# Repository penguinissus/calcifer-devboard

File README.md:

# Calcifer Devboard
Calcifer Devboard is a funny take on the RP2040 Devboard. It contains all of the basic components of what a devboard usually has like SRAM, processors, USB controllers, and breakout pins. The interesting twist on this devboard is that it is shaped like Calcifer, a character from Howl's Moving Castle.  

# Features
- USB-C Port  
- 12MHz Crystal Oscillator  
- 16mb Flash Storage
- 29 I/O Pins  

# Why did I make it
If you don't know the story behind Howl's Moving Castle, Calcifer is a fire demon that is trapped inside Howl's Castle and he powers and controls all of the magical things that the castle does. To me, this seemed parallel to what a devboard does in any electronics project, since a devboard is basically the heart and soul and would control all of the other components around it. 

# Diagrams
This schematic diagram looks the exact same as the guide from kaipereira.  
  
This is what my devboard looked like in the PCB editor. You can see that it has the outline and silkscreen of calcifer on it.  
  
This is what the front of the PCB should look like when it is built properly. The frontside only shows a silkscreen of calcifer and is not obstructed by any components.  
  
This is what the back of the PCB should look like. All of the components are on this side and all of the pins are clearly labeled. There is also a label saying this is made by me.  

# Resource
This project is all thanks to [kaipereira's guide](https://github.com/KaiPereira/build-a-devboard/blob/master/README.md) on designing an RP2040 devboard. 

# How to use
This is just a devboard so there isn't really a step-by-step assembly or firmware isntructions.

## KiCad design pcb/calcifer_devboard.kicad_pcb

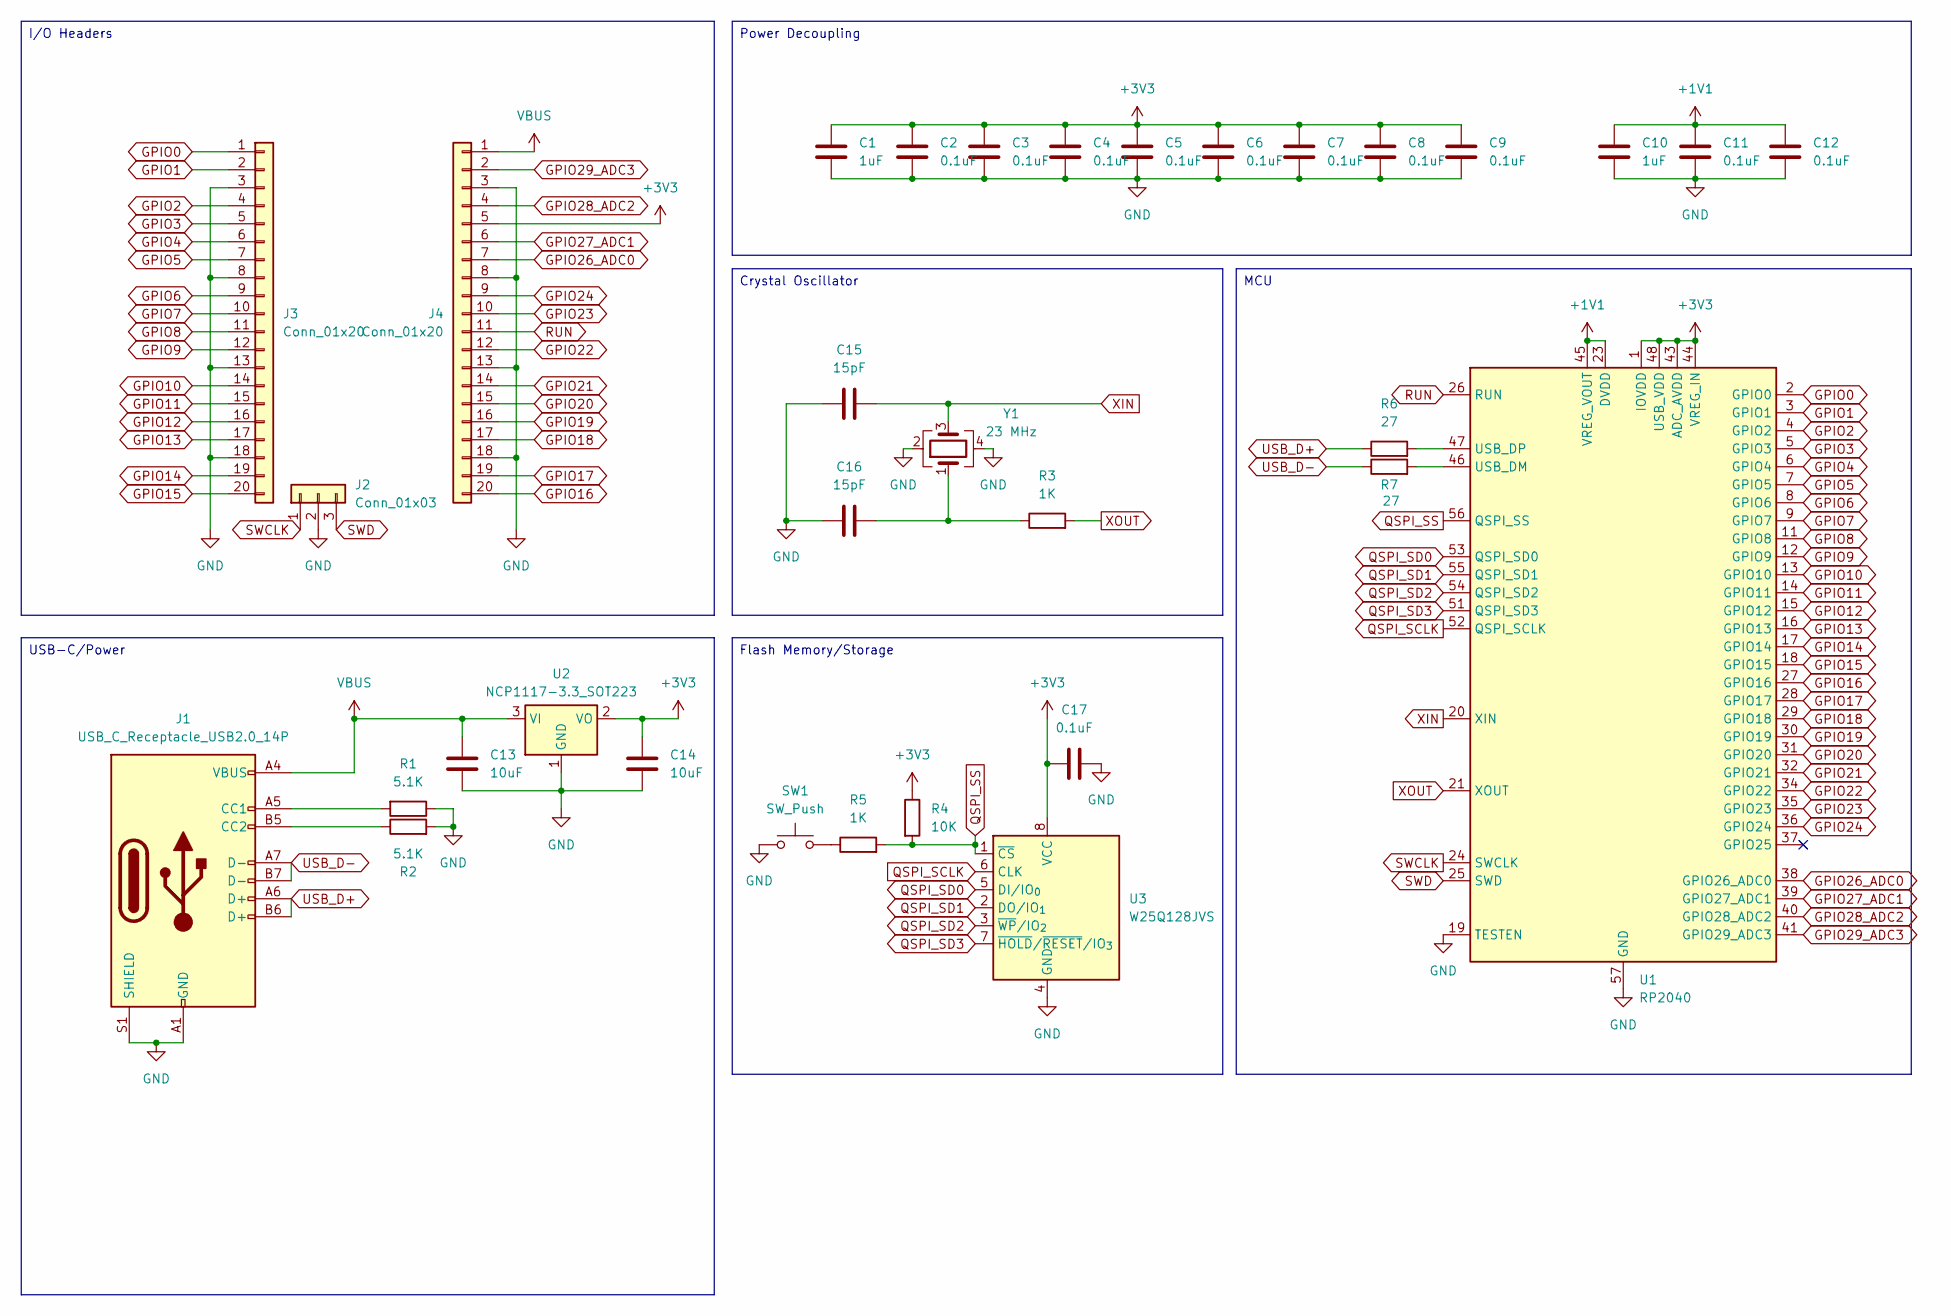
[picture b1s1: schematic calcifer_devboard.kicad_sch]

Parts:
C1, C10: 1uF; C_0402_1005Metric
C2, C3, C4, C5, C6, C7, C8, C9, C11, C12, C17: 0.1uF; C_0402_1005Metric
C13, C14: 10uF; C_0402_1005Metric
C15, C16: 15pF; C_0402_1005Metric
J1: USB_C_Receptacle_USB2.0_14P; USB_C_Receptacle_HRO_TYPE-C-31-M-12
J2: Conn_01x03; PinSocket_1x03_P2.54mm_Vertical
J3, J4: Conn_01x20; PinSocket_1x20_P2.54mm_Vertical
R1, R2: 5.1K; R_0402_1005Metric
R3, R5: 1K; R_0402_1005Metric
R4: 10K; R_0402_1005Metric
R6, R7: 27; R_0402_1005Metric
SW1: SW_Push; SW_Push_SPST_NO_Alps_SKRK
U1: RP2040; QFN-56-1EP_7x7mm_P0.4mm_EP3.2x3.2mm
U2: NCP1117-3.3_SOT223; SOT-223-3_TabPin2
U3: W25Q128JVS; SOIC-8_5.3x5.3mm_P1.27mm
Y1: 23 MHz; Crystal_SMD_3225-4Pin_3.2x2.5mm

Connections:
+1V1: C10.1, C11.1, C12.1, U1.23 (DVDD), U1.45 (VREG_VOUT), U1.50 (DVDD)
+3V3: C1.1, C2.1, C3.1, C4.1, C5.1, C6.1, C7.1, C8.1, C9.1, C14.1, C17.2, J4.5, R4.1, U1.1 (IOVDD), U1.10 (IOVDD), U1.22 (IOVDD), U1.33 (IOVDD), U1.42 (IOVDD), U1.43 (ADC_AVDD), U1.44 (VREG_IN), U1.48 (USB_VDD), U1.49 (IOVDD), U2.2 (VO), U3.8 (VCC)
GND: C1.2, C2.2, C3.2, C4.2, C5.2, C6.2, C7.2, C8.2, C9.2, C10.2, C11.2, C12.2, C13.2, C14.2, C15.1, C16.2, C17.1, J1.A1 (GND), J1.A12 (GND), J1.B1 (GND), J1.B12 (GND), J1.S1 (SHIELD), J2.2, J3.3, J3.8, J3.13, J3.18, J4.3, J4.8, J4.13, J4.18, R1.1, R2.2, SW1.1, U1.19 (TESTEN), U1.57 (GND), U2.1 (GND), U3.4 (GND), Y1.2, Y1.4
GPIO0: J3.1, U1.2 (GPIO0)
GPIO1: J3.2, U1.3 (GPIO1)
GPIO2: J3.4, U1.4 (GPIO2)
GPIO3: J3.5, U1.5 (GPIO3)
GPIO4: J3.6, U1.6 (GPIO4)
GPIO5: J3.7, U1.7 (GPIO5)
GPIO6: J3.9, U1.8 (GPIO6)
GPIO7: J3.10, U1.9 (GPIO7)
GPIO8: J3.11, U1.11 (GPIO8)
GPIO9: J3.12, U1.12 (GPIO9)
GPIO10: J3.14, U1.13 (GPIO10)
GPIO11: J3.15, U1.14 (GPIO11)
GPIO12: J3.16, U1.15 (GPIO12)
GPIO13: J3.17, U1.16 (GPIO13)
GPIO14: J3.19, U1.17 (GPIO14)
GPIO15: J3.20, U1.18 (GPIO15)
GPIO16: J4.20, U1.27 (GPIO16)
GPIO17: J4.19, U1.28 (GPIO17)
GPIO18: J4.17, U1.29 (GPIO18)
GPIO19: J4.16, U1.30 (GPIO19)
GPIO20: J4.15, U1.31 (GPIO20)
GPIO21: J4.14, U1.32 (GPIO21)
GPIO22: J4.12, U1.34 (GPIO22)
GPIO23: J4.10, U1.35 (GPIO23)
GPIO24: J4.9, U1.36 (GPIO24)
GPIO26_ADC0: J4.7, U1.38 (GPIO26_ADC0)
GPIO27_ADC1: J4.6, U1.39 (GPIO27_ADC1)
GPIO28_ADC2: J4.4, U1.40 (GPIO28_ADC2)
GPIO29_ADC3: J4.2, U1.41 (GPIO29_ADC3)
unnamed: C16.1, R3.1, Y1.1
unnamed: J1.A5 (CC1), R1.2
unnamed: J1.B5 (CC2), R2.1
unnamed: R5.1, SW1.2
unnamed: R7.2, U1.46 (USB_DM)
unnamed: R6.2, U1.47 (USB_DP)
QSPI_SCLK: U1.52 (QSPI_SCLK), U3.6 (CLK)
QSPI_SD0: U1.53 (QSPI_SD0), U3.5 (DI/IO_{0})
QSPI_SD1: U1.55 (QSPI_SD1), U3.2 (DO/IO_{1})
QSPI_SD2: U1.54 (QSPI_SD2), U3.3 (~WP/IO_{2})
QSPI_SD3: U1.51 (QSPI_SD3), U3.7 (~HOLD/~RESET/IO_{3})
QSPI_SS: R4.2, R5.2, U1.56 (QSPI_SS), U3.1 (~CS)
RUN: J4.11, U1.26 (RUN)
SWCLK: J2.1, U1.24 (SWCLK)
SWD: J2.3, U1.25 (SWD)
USB_D+: J1.A6 (D+), J1.B6 (D+), R6.1
USB_D-: J1.A7 (D-), J1.B7 (D-), R7.1
VBUS: C13.1, J1.A4 (VBUS), J1.A9 (VBUS), J1.B4 (VBUS), J1.B9 (VBUS), J4.1, U2.3 (VI)
XIN: C15.2, U1.20 (XIN), Y1.3
XOUT: R3.2, U1.21 (XOUT)

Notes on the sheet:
Flash Memory/Storage
Power Decoupling
I/O Headers
Crystal Oscillator
USB-C/Power
MCU

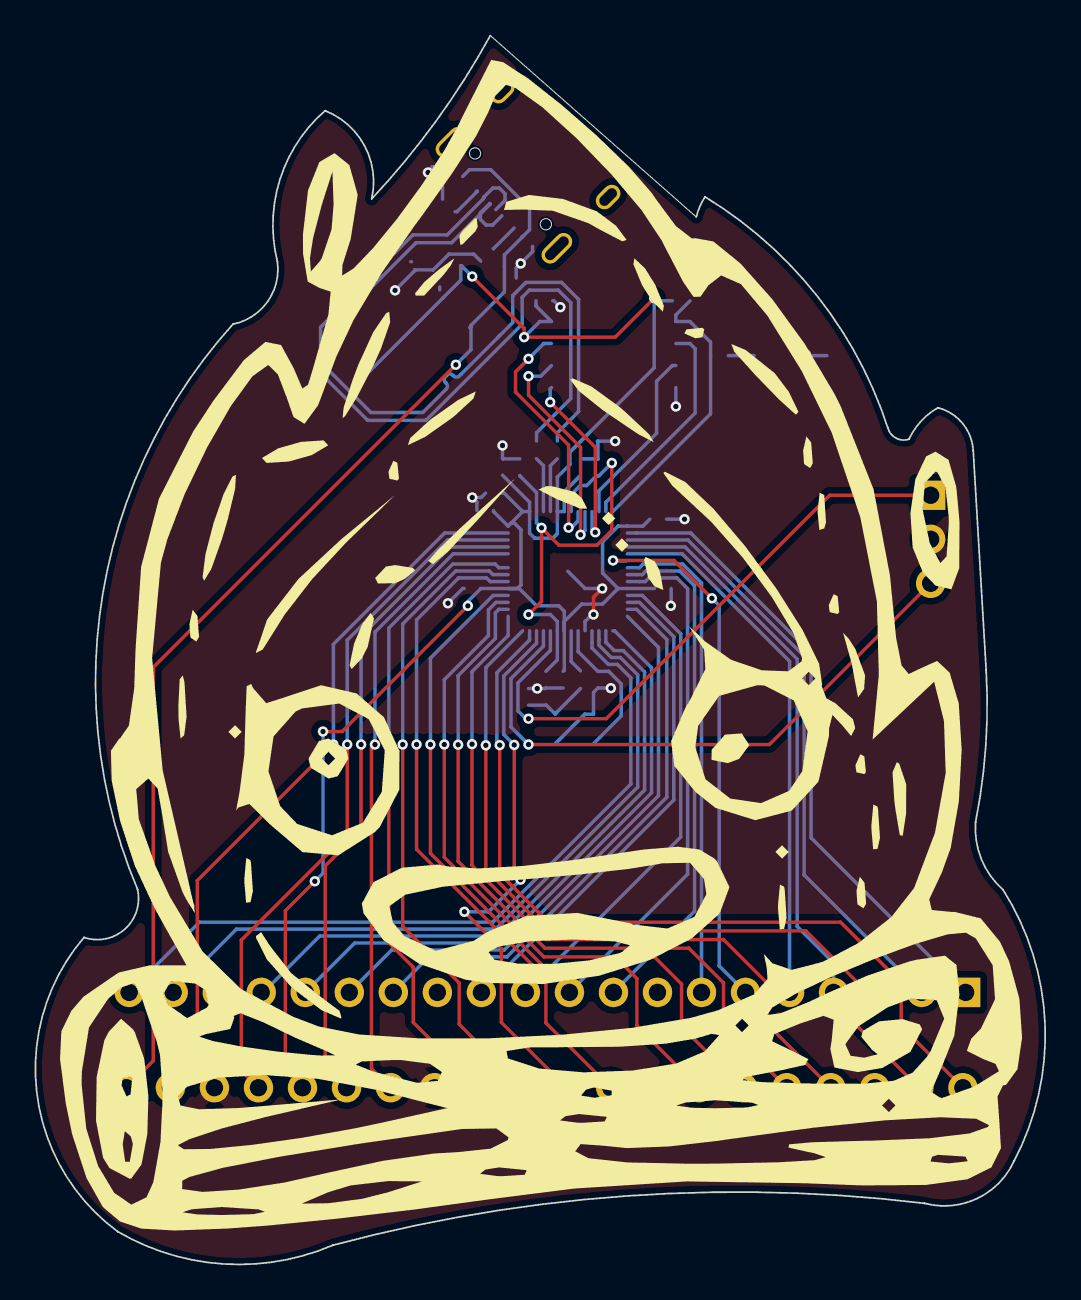
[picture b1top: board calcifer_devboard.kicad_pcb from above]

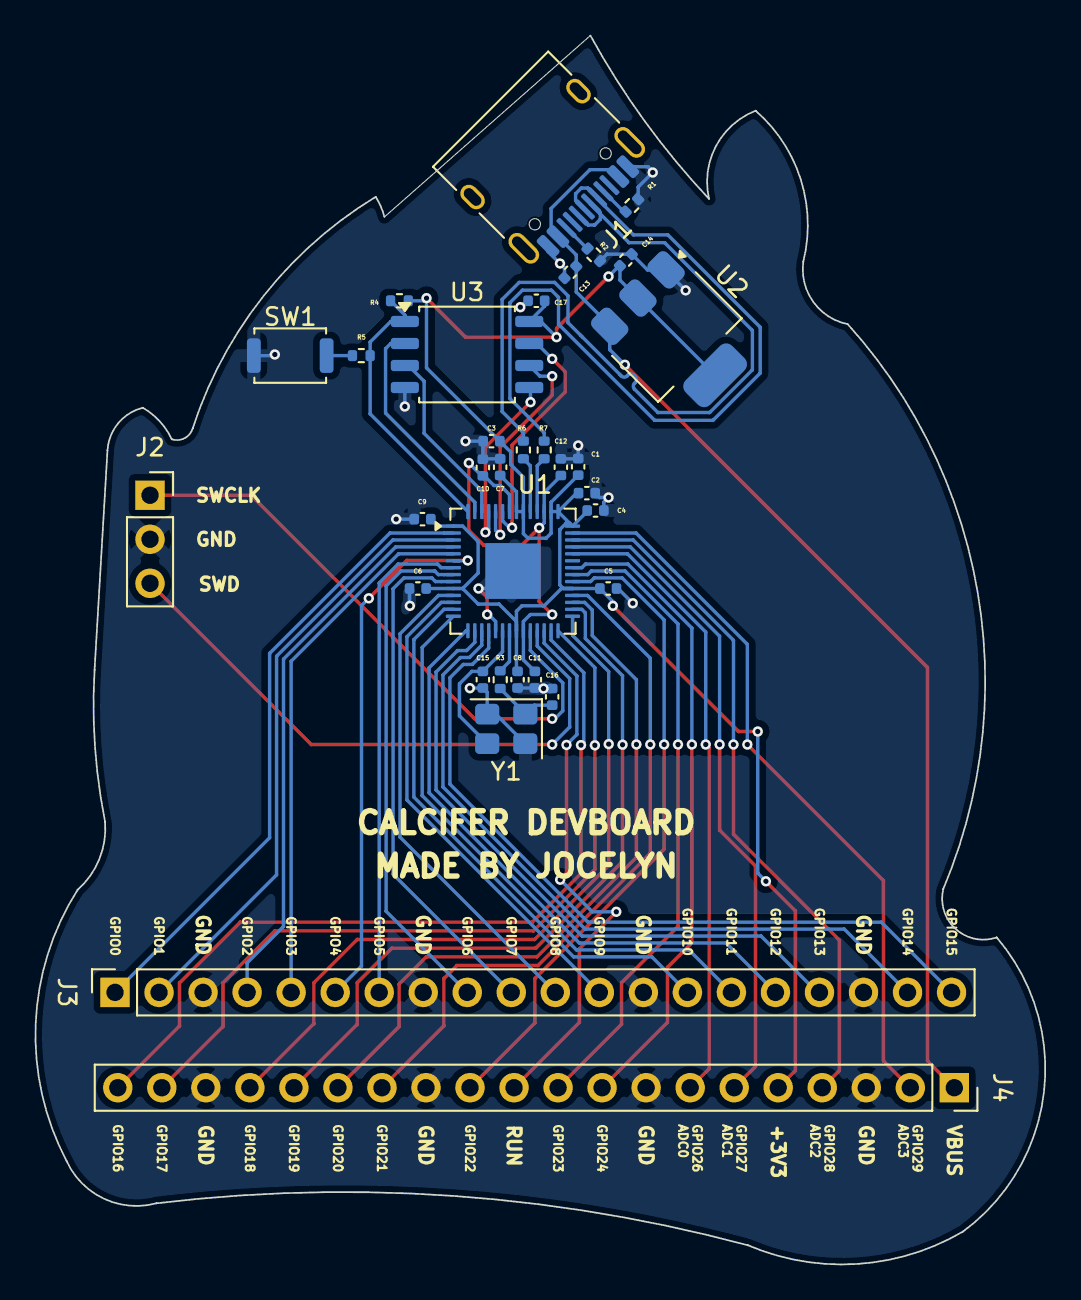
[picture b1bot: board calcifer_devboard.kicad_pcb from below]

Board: 2 copper layers, 58.2 x 70.9 mm, 33 parts (33 on the bottom side), 52 nets.

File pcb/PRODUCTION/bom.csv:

Designator,Footprint,Quantity,Value,LCSC Part #
"C1, C10",0402,2,1uF,
"C11, C12, C17, C2, C3, C4, C5, C6, C7, C8, C9",0402,11,0.1uF,
"C13, C14",0402,2,10uF,
"C15, C16",0402,2,15pF,
J1,USB_C_Receptacle_HRO_TYPE-C-31-M-12,1,USB_C_Receptacle_USB2.0_14P,
J2,PinSocket_1x03_P2.54mm_Vertical,1,Conn_01x03,
"J3, J4",PinSocket_1x20_P2.54mm_Vertical,2,Conn_01x20,
"R1, R2",0402,2,5.1K,
"R3, R5",0402,2,1K,
R4,0402,1,10K,
"R6, R7",0402,2,27,
SW1,SW_Push_SPST_NO_Alps_SKRK,1,SW_Push,
U1,QFN-56-1EP_7x7mm_P0.4mm_EP3.2x3.2mm,1,RP2040,
U2,SOT-223-3_TabPin2,1,NCP1117-3.3_SOT223,
U3,SOIC-8_5.3x5.3mm_P1.27mm,1,W25Q128JVS,
Y1,Crystal_SMD_3225-4Pin_3.2x2.5mm,1,23 MHz,

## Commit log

2026-06-16 edit README.md
2026-06-17 Completed README.md
2026-06-17 retraced everything and finished readme
2026-06-18 Silkscreen update and complete README
2026-06-19 updated README and added production files
2026-06-19 fallout zine
2026-06-19 reorganize repository
2026-06-19 reorganize repo
2026-06-19 update readme filepaths
